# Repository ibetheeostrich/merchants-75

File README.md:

# merchants-60
 Merchant's Guild Standard 60

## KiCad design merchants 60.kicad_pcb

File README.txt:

```````````````````````````````````````
Merchants 60 (should be changed to 75)

```````````````````````````````````````
Github repo found @:
	https://github.com/ibetheeostrich/merchants-60

Resources used:
	ai03's Keyboard PCB Design Guide
	https://wiki.ai03.com/books/pcb-design/page/pcb-guide-part-1---preparations

	ruiqimao/keyboard-pcb-guide
	https://github.com/ruiqimao/keyboard-pcb-guide

	Intro to KiCad
	https://www.youtube.com/playlist?list=PLEBQazB0HUyR24ckSZ5u05TZHV9khgA1O

	When should I coose 2 layer PCB or 4 layer PCB?
	https://www.pcbgogo.com/blog/When_should_I_choose_2_layer_PCB_or_4_layer_PCB_.html#:~:text=2%20layers%20PCB%20has%20two,layers%20PCB%20has%204%20layers.&text=However%2C%20it's%20better%20to%20use,four%20copper%20layers%20laminated%20together.

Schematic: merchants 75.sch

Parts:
C1, C3: 0.1uF; C_0805_2012Metric
C2: 0.1uf; C_0805_2012Metric
C4, C5: 22pF; C_0805_2012Metric
C6: 10uF; C_0805_2012Metric
C7: 1uF; C_0805_2012Metric
D1, D2, D3, D4, D5, D6, D7, D8, D9, D10, D11, D12, D13, D14, D15, D16, D17, D18, D19, D20, D21, D22, D23, D24, D25, D26, D27, D28, D29, D30, D31, D32, D33, D34, D35, D36, D37, D38, D39, D40, D41, D42, D43, D44, D45, D46, D47, D48, D49, D50, D51, D52, D53, D54, D55, D56, D57, D58, D59, D60, D61, D62, D63, D64, D65, D66, D67, D68, D69, D70, D71, D72, D73, D74, D75, D76, D77, D78, D79, D80, D81, D82, D83: D; D_SOD123_axial
F1: 500mA; Fuse_1206_3216Metric
MX1, MX2, MX7, MX8, MX9, MX10, MX11, MX13, MX14, MX15, MX16, MX17, MX19, MX20, MX21, MX22, MX23, MX24, MX25, MX26, MX27, MX28, MX29, MX30, MX31, MX32, MX33, MX35, MX36, MX37, MX38, MX39, MX40, MX41, MX42, MX43, MX44, MX45, MX46, MX47, MX48, MX49, MX50, MX51, MX52, MX53, MX54, MX56, MX57, MX58, MX59, MX60, MX61, MX62, MX63, MX64, MX65, MX66, MX67, MX69, MX72, MX73, MX76, MX77, MX78, MX79, MX80, MX81, MX82, MX83: MX-NoLED; MX-1U-NoLED
MX3, MX55, MX68, MX75: MX-NoLED; MX-1.5U-NoLED
MX4, MX71: MX-NoLED; MX-1.75U-NoLED
MX5, MX70: MX-NoLED; MX-2.25U-NoLED
MX6, MX12, MX18: MX-NoLED; MX-1.25U-NoLED
MX34: MX-NoLED; MX-6.25U-NoLED
MX74: MX-NoLED; MX-2U-NoLED
R1, R2: 22; R_0805_2012Metric
R3, R4: 10k; R_0805_2012Metric
U1: ATmega32U4-AU; TQFP-44_10x10mm_P0.8mm
USB1: Molex-0548190589; USB_miniB
Y1: 16MHz; Crystal_SMD_3225-4Pin_3.2x2.5mm

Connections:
+5V: C1.1, C2.1, C3.2, C6.1, F1.2, R3.1, U1.2 (UVCC), U1.7 (VBUS), U1.14 (VCC), U1.24 (AVCC), U1.34 (VCC), U1.44 (AVCC)
D+: R2.2, USB1.3 (D+)
D-: R1.2, USB1.4 (D-)
GND: C1.2, C2.2, C3.1, C4.2, C5.1, C6.2, C7.2, R4.1, U1.5 (UGND), U1.15 (GND), U1.23 (GND), U1.35 (GND), U1.43 (GND), USB1.1 (GND), Y1.2, Y1.4; also elsewhere on the board
unnamed: C4.1, U1.17 (XTAL1), Y1.1
unnamed: C5.2, U1.16 (XTAL2), Y1.3
unnamed: C7.1, U1.6 (UCAP)
unnamed: D1.2 (A), MX1.2 (ROW)
unnamed: D2.2 (A), MX2.2 (ROW)
unnamed: D3.2 (A), MX3.2 (ROW)
unnamed: D4.2 (A), MX4.2 (ROW)
unnamed: D5.2 (A), MX5.2 (ROW)
unnamed: D6.2 (A), MX6.2 (ROW)
unnamed: D7.2 (A), MX7.2 (ROW)
unnamed: D8.2 (A), MX8.2 (ROW)
unnamed: D9.2 (A), MX9.2 (ROW)
unnamed: D10.2 (A), MX10.2 (ROW)
unnamed: D11.2 (A), MX11.2 (ROW)
unnamed: D12.2 (A), MX12.2 (ROW)
unnamed: D13.2 (A), MX13.2 (ROW)
unnamed: D14.2 (A), MX14.2 (ROW)
unnamed: D15.2 (A), MX15.2 (ROW)
unnamed: D16.2 (A), MX16.2 (ROW)
unnamed: D17.2 (A), MX17.2 (ROW)
unnamed: D18.2 (A), MX18.2 (ROW)
unnamed: D19.2 (A), MX19.2 (ROW)
unnamed: D20.2 (A), MX20.2 (ROW)
unnamed: D21.2 (A), MX21.2 (ROW)
unnamed: D22.2 (A), MX22.2 (ROW)
unnamed: D23.2 (A), MX23.2 (ROW)
unnamed: D24.2 (A), MX24.2 (ROW)
unnamed: D25.2 (A), MX25.2 (ROW)
unnamed: D26.2 (A), MX26.2 (ROW)
unnamed: D27.2 (A), MX27.2 (ROW)
unnamed: D28.2 (A), MX28.2 (ROW)
unnamed: D29.2 (A), MX29.2 (ROW)
unnamed: D30.2 (A), MX30.2 (ROW)
unnamed: D31.2 (A), MX31.2 (ROW)
unnamed: D32.2 (A), MX32.2 (ROW)
unnamed: D33.2 (A), MX33.2 (ROW)
unnamed: D34.2 (A), MX34.2 (ROW)
unnamed: D35.2 (A), MX35.2 (ROW)
unnamed: D36.2 (A), MX36.2 (ROW)
unnamed: D37.2 (A), MX37.2 (ROW)
unnamed: D38.2 (A), MX38.2 (ROW)
unnamed: D39.2 (A), MX39.2 (ROW)
unnamed: D40.2 (A), MX40.2 (ROW)
unnamed: D41.2 (A), MX41.2 (ROW)
unnamed: D42.2 (A), MX42.2 (ROW)
unnamed: D43.2 (A), MX43.2 (ROW)
unnamed: D44.2 (A), MX44.2 (ROW)
unnamed: D45.2 (A), MX45.2 (ROW)
unnamed: D46.2 (A), MX46.2 (ROW)
unnamed: D47.2 (A), MX47.2 (ROW)
unnamed: D48.2 (A), MX48.2 (ROW)
unnamed: D49.2 (A), MX49.2 (ROW)
unnamed: D50.2 (A), MX50.2 (ROW)
unnamed: D51.2 (A), MX51.2 (ROW)
unnamed: D52.2 (A), MX52.2 (ROW)
unnamed: D53.2 (A), MX53.2 (ROW)
unnamed: D54.2 (A), MX54.2 (ROW)
unnamed: D55.2 (A), MX55.2 (ROW)
unnamed: D56.2 (A), MX56.2 (ROW)
unnamed: D57.2 (A), MX57.2 (ROW)
unnamed: D58.2 (A), MX58.2 (ROW)
unnamed: D59.2 (A), MX59.2 (ROW)
unnamed: D60.2 (A), MX60.2 (ROW)
unnamed: D61.2 (A), MX61.2 (ROW)
unnamed: D62.2 (A), MX62.2 (ROW)
unnamed: D63.2 (A), MX63.2 (ROW)
unnamed: D64.2 (A), MX64.2 (ROW)
unnamed: D65.2 (A), MX65.2 (ROW)
unnamed: D66.2 (A), MX66.2 (ROW)
unnamed: D67.2 (A), MX67.2 (ROW)
unnamed: D68.2 (A), MX68.2 (ROW)
unnamed: D69.2 (A), MX69.2 (ROW)
unnamed: D70.2 (A), MX70.2 (ROW)
unnamed: D71.2 (A), MX71.2 (ROW)
unnamed: D72.2 (A), MX72.2 (ROW)
unnamed: D73.2 (A), MX73.2 (ROW)
unnamed: D74.2 (A), MX74.2 (ROW)
unnamed: D75.2 (A), MX75.2 (ROW)
unnamed: D76.2 (A), MX76.2 (ROW)
unnamed: D77.2 (A), MX77.2 (ROW)
unnamed: D78.2 (A), MX78.2 (ROW)
unnamed: D79.2 (A), MX79.2 (ROW)
unnamed: D80.2 (A), MX80.2 (ROW)
unnamed: D81.2 (A), MX81.2 (ROW)
unnamed: D82.2 (A), MX82.2 (ROW)
unnamed: D83.2 (A), MX83.2 (ROW)
unnamed: R1.1, U1.3 (D-)
unnamed: R2.1, U1.4 (D+)
unnamed 92: R3.2, U1.13 (~RESET); also elsewhere on the board
unnamed: R4.2, U1.33 (~HWB~/PE2)
VCC: F1.1, USB1.5 (VBUS)
col0: MX1.1 (COL), MX2.1 (COL), MX3.1 (COL), MX4.1 (COL), MX5.1 (COL), MX6.1 (COL), U1.19 (PD1)
col1: MX7.1 (COL), MX8.1 (COL), MX9.1 (COL), MX10.1 (COL), MX11.1 (COL), MX12.1 (COL), U1.20 (PD2)
col2: MX13.1 (COL), MX14.1 (COL), MX15.1 (COL), MX16.1 (COL), MX17.1 (COL), MX18.1 (COL), U1.21 (PD3)
col3: MX19.1 (COL), MX20.1 (COL), MX21.1 (COL), MX22.1 (COL), MX23.1 (COL), U1.41 (PF0)
col4: MX24.1 (COL), MX25.1 (COL), MX26.1 (COL), MX27.1 (COL), MX28.1 (COL), U1.40 (PF1)
col5: MX29.1 (COL), MX30.1 (COL), MX31.1 (COL), MX32.1 (COL), MX33.1 (COL), MX34.1 (COL), U1.39 (PF4)
col6: MX35.1 (COL), MX36.1 (COL), MX37.1 (COL), MX38.1 (COL), MX39.1 (COL), U1.38 (PF5)
col7: MX40.1 (COL), MX41.1 (COL), MX42.1 (COL), MX43.1 (COL), MX44.1 (COL), U1.37 (PF6)
col8: MX45.1 (COL), MX46.1 (COL), MX47.1 (COL), MX48.1 (COL), MX49.1 (COL), U1.36 (PF7)
col9: MX50.1 (COL), MX51.1 (COL), MX52.1 (COL), MX53.1 (COL), MX54.1 (COL), MX55.1 (COL), U1.32 (PC7)
col10: MX56.1 (COL), MX57.1 (COL), MX58.1 (COL), MX59.1 (COL), MX60.1 (COL), U1.31 (PC6)
col11: MX61.1 (COL), MX62.1 (COL), MX63.1 (COL), MX64.1 (COL), U1.30 (PB6)
col12: MX65.1 (COL), MX66.1 (COL), MX67.1 (COL), MX68.1 (COL), U1.29 (PB5)
col13: MX69.1 (COL), MX70.1 (COL), MX71.1 (COL), MX72.1 (COL), U1.28 (PB4)
col14: MX73.1 (COL), MX74.1 (COL), MX75.1 (COL), MX76.1 (COL), MX77.1 (COL), U1.27 (PD7)
col15: MX78.1 (COL), MX79.1 (COL), MX80.1 (COL), MX81.1 (COL), MX82.1 (COL), MX83.1 (COL), U1.26 (PD6)
row0: D1.1 (K), D7.1 (K), D13.1 (K), D19.1 (K), D24.1 (K), D29.1 (K), D35.1 (K), D40.1 (K), D45.1 (K), D50.1 (K), D56.1 (K), D61.1 (K), D65.1 (K), D69.1 (K), D73.1 (K), D78.1 (K), U1.11 (PB3)
row1: D2.1 (K), D8.1 (K), D14.1 (K), D20.1 (K), D25.1 (K), D30.1 (K), D36.1 (K), D41.1 (K), D46.1 (K), D51.1 (K), D57.1 (K), D62.1 (K), D66.1 (K), D74.1 (K), D79.1 (K), U1.18 (PD0)
row2: D3.1 (K), D9.1 (K), D15.1 (K), D21.1 (K), D26.1 (K), D31.1 (K), D37.1 (K), D42.1 (K), D47.1 (K), D52.1 (K), D58.1 (K), D63.1 (K), D67.1 (K), D75.1 (K), D80.1 (K), U1.22 (PD5)
row3: D4.1 (K), D10.1 (K), D16.1 (K), D22.1 (K), D27.1 (K), D32.1 (K), D38.1 (K), D43.1 (K), D48.1 (K), D53.1 (K), D59.1 (K), D64.1 (K), D70.1 (K), D81.1 (K), U1.8 (PB0)
row4: D5.1 (K), D11.1 (K), D17.1 (K), D23.1 (K), D28.1 (K), D33.1 (K), D39.1 (K), D44.1 (K), D49.1 (K), D54.1 (K), D60.1 (K), D71.1 (K), D76.1 (K), D82.1 (K), U1.9 (PB1)
row5: D6.1 (K), D12.1 (K), D18.1 (K), D34.1 (K), D55.1 (K), D68.1 (K), D72.1 (K), D77.1 (K), D83.1 (K), U1.10 (PB2)

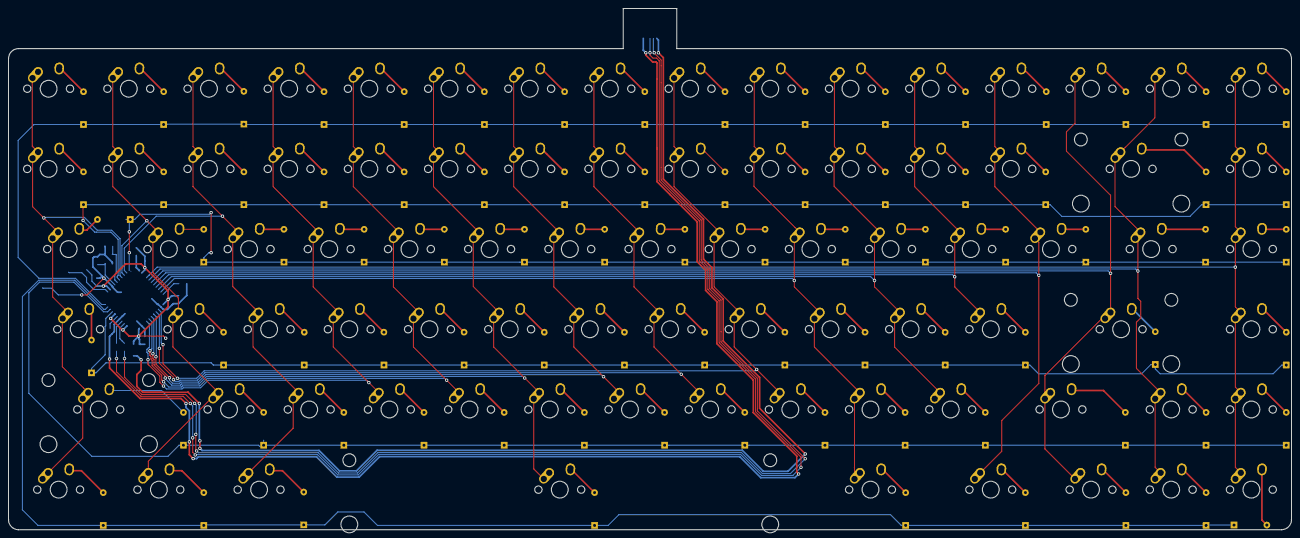
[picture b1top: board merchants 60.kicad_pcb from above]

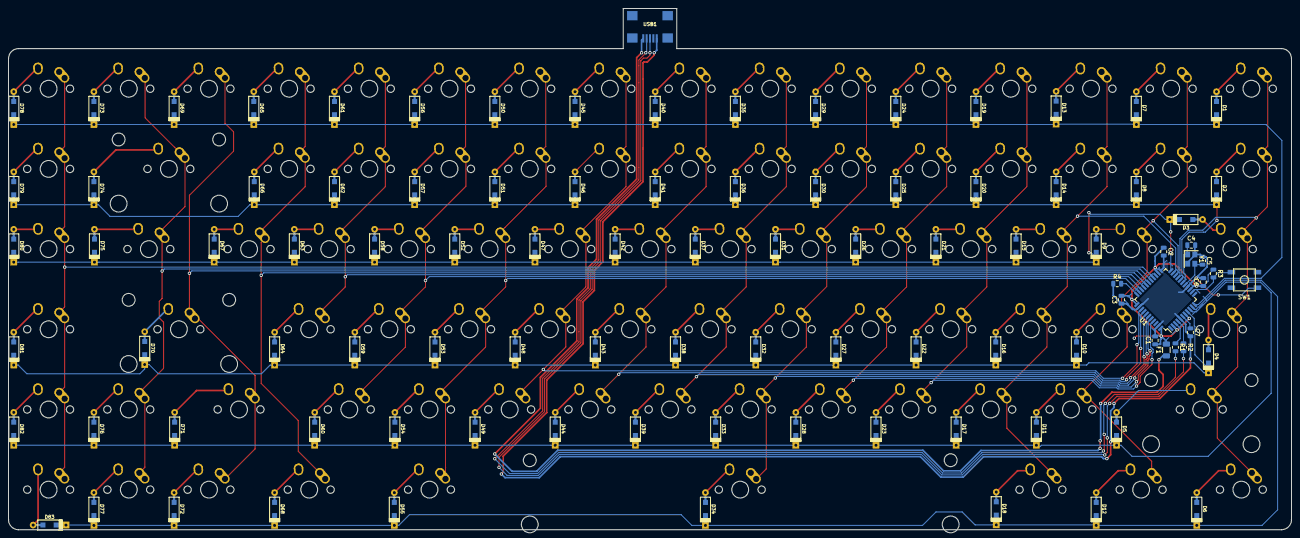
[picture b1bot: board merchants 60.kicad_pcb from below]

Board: 2 copper layers, 304.8 x 123.8 mm, 182 parts (99 on the bottom side), 117 nets.

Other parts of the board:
SW1: SW_PUSH; SKQG-1155865

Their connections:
GND: SW1.1; also elsewhere on the board
unnamed 92: SW1.2; also elsewhere on the board

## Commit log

2020-09-25 Initialise Project
2020-09-25 Add submodules
2020-09-25 Adding footprint libraries
2020-09-25 Assigning Footprints and Shit
2020-09-27 Finalising PCB and Generating Gerbers
2020-09-27 Converting the PCB from 4 layer to 2 layer
    Im fucking retarded but I'm also a fucking god
2020-09-27 Minor Changes
2020-10-01 slight routing changes
2020-10-03 Rerouting traces
2020-11-08 3D Models
    Creating 3D Models of Cases
2020-12-24 minor fanangling
2020-12-24 File Arranging
2020-12-24 pics
